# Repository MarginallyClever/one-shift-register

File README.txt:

Shift registers: what are they, how do they work, and some pratical examples.

See https://www.marginallyclever.com/2017/02/use-74hc959-shift-register/
for the tutorial, discussion, and lots of other great stuff.

Please support our work: Like, share, and buy from marginallyclever.com today.  Thank you!

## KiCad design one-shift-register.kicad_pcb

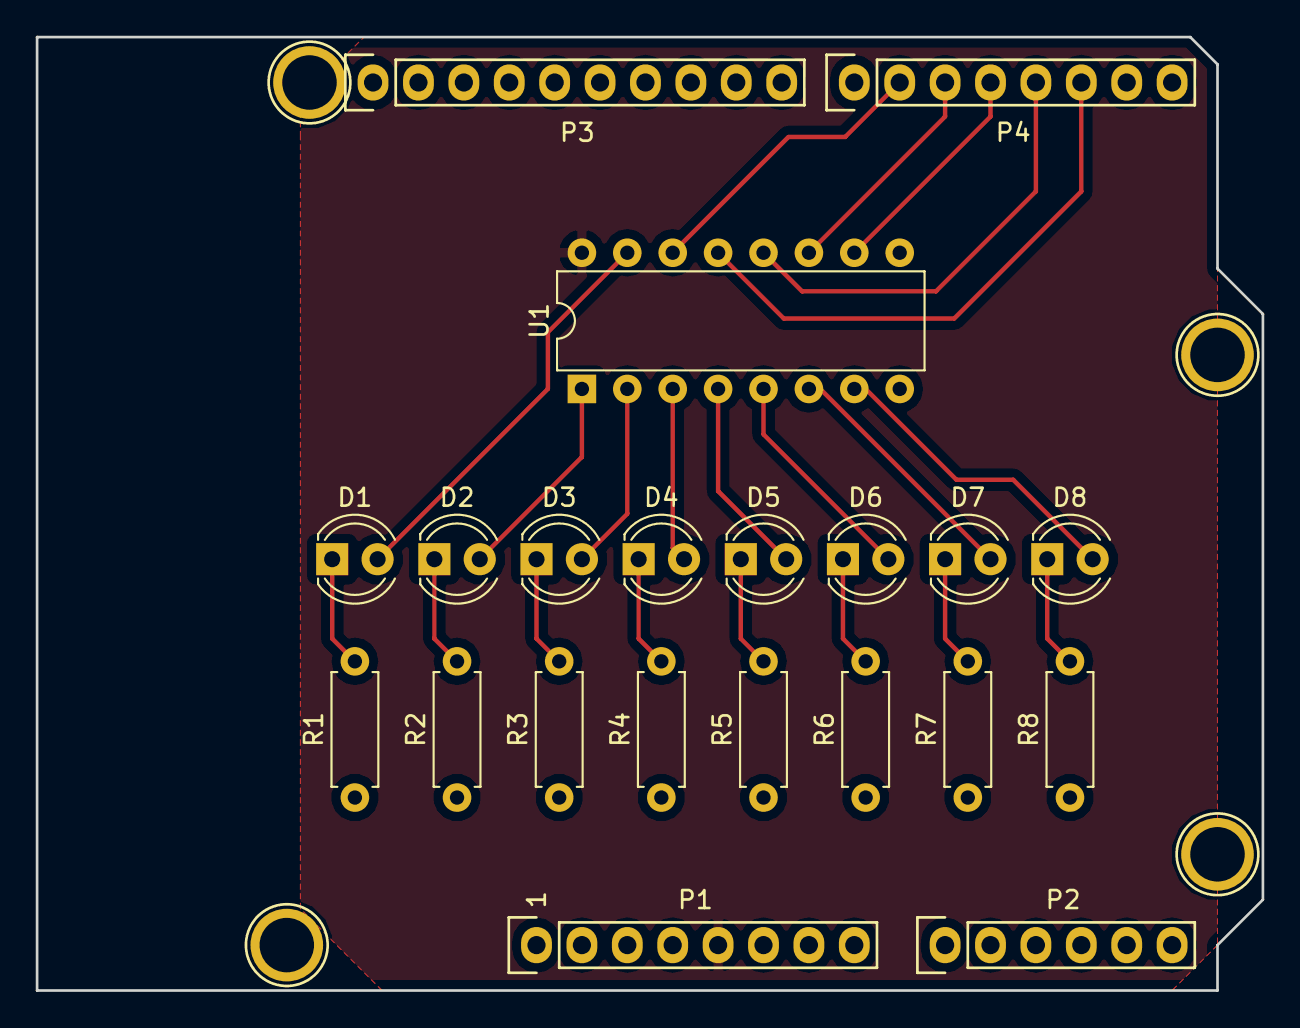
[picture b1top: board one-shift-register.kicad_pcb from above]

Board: 2 copper layers, 68.6 x 53.3 mm, 25 parts (0 on the bottom side), 23 nets.

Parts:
D1, D2, D3, D4, D5, D6, D7, D8: LED; LED_D4.0mm
P1: Power; Socket_Strip_Arduino_1x08
P2: Analog; Socket_Strip_Arduino_1x06
P3: Digital; Socket_Strip_Arduino_1x10
P4: Digital; Socket_Strip_Arduino_1x08
P5, P6, P7, P8: CONN_1; Arduino_1pin
R1, R2, R3, R4, R5, R6, R7, R8: 220; R_Axial_DIN0207_L6.3mm_D2.5mm_P7.62mm_Horizontal
U1: 74HC595; DIP-16_W7.62mm

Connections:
+5V: P1.5, U1.16
/2: P4.6, U1.13
/3(**): P4.5, U1.12
/4: P4.4, U1.10
/5(**): P4.3, U1.11
/6(**): P4.2, U1.14
GND: P1.6, P1.7, P3.4, R1.1, R2.1, R3.1, R4.1, R5.1, R6.1, R7.1, R8.1, U1.8
unnamed: D1.1, R1.2
unnamed: D1.2, U1.15
unnamed: D2.1, R2.2
unnamed: D2.2, U1.1
unnamed: D3.1, R3.2
unnamed: D3.2, U1.2
unnamed: D4.1, R4.2
unnamed: D4.2, U1.3
unnamed: D5.1, R5.2
unnamed: D5.2, U1.4
unnamed: D6.1, R6.2
unnamed: D6.2, U1.5
unnamed: D7.1, R7.2
unnamed: D7.2, U1.6
unnamed: D8.1, R8.2
unnamed: D8.2, U1.7

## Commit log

2017-02-14 :neckbeard: Added .gitattributes & .gitignore files
2017-02-15 added text to PCB; turned on all arduino demos
